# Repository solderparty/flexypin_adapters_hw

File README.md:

# FlexyPin Adapters

To learn more about FlexyPins, see the dedicated repo here: https://github.com/solderparty/flexypin

This repo contains a collection of open hardware designs for common modules that can be used with FlexyPins.

## ESP-12

## ESP32-C3-WROOM

## ESP32-S2-SOLO / ESP32-S3-WROOM

## ESP32-WROOM

## ESP32-WROVER

## M5Stamp-Pico

## RaspberryPi Pico

## RaspberryPi Pico to Uno

## RaspberryPi RM2

## RFM9x

## WIO RP2040

## Xiao / QTPy

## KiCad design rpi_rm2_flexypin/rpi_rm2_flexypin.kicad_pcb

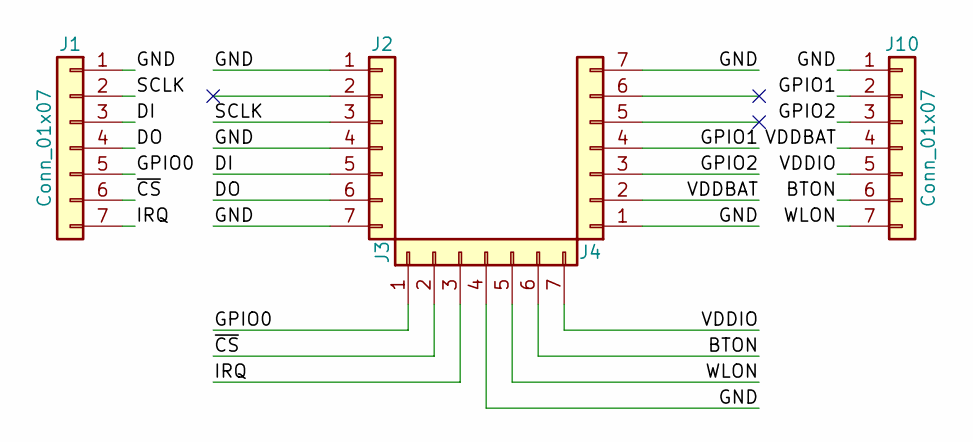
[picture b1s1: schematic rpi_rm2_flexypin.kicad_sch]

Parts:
J1, J10: Conn_01x07; PinHeader_1x07_P2.54mm_Vertical
J2, J3, J4: Conn_01x07; FlexyPin_1x07_P1.50mm

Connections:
/BTON: J3.6, J10.6
/DI: J1.3, J2.5
/DO: J1.4, J2.6
/GND: J1.1, J2.1, J2.4, J2.7, J3.4, J4.1, J4.7, J10.1
/GPIO0: J1.5, J3.1
/GPIO1: J4.4, J10.2
/GPIO2: J4.3, J10.3
/IRQ: J1.7, J3.3
/SCLK: J1.2, J2.3
/VDDBAT: J4.2, J10.4
/VDDIO: J3.7, J10.5
/WLON: J3.5, J10.7
/~CS: J1.6, J3.2

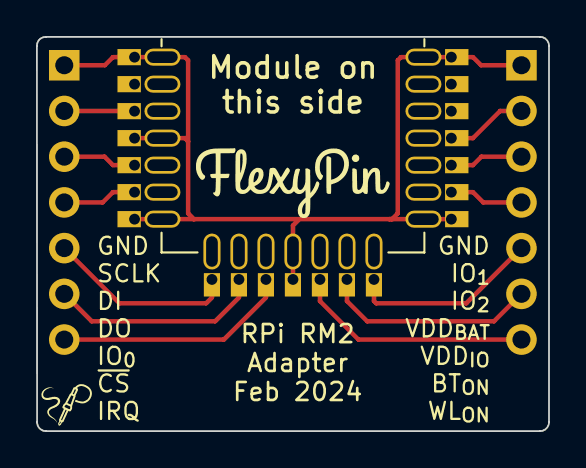
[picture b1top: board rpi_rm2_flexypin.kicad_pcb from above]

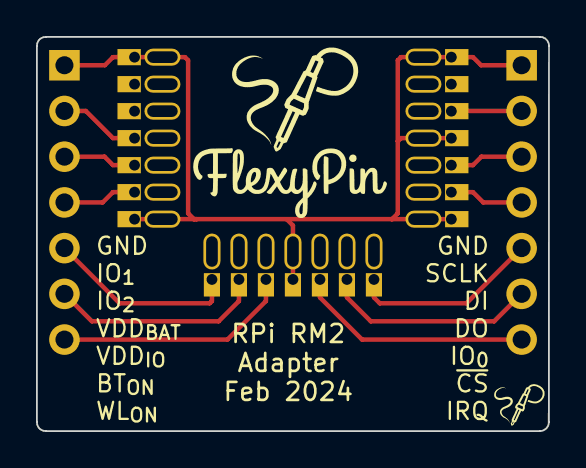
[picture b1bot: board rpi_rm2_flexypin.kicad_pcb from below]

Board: 2 copper layers, 28.5 x 21.9 mm, 5 parts (2 on the bottom side), 13 nets.

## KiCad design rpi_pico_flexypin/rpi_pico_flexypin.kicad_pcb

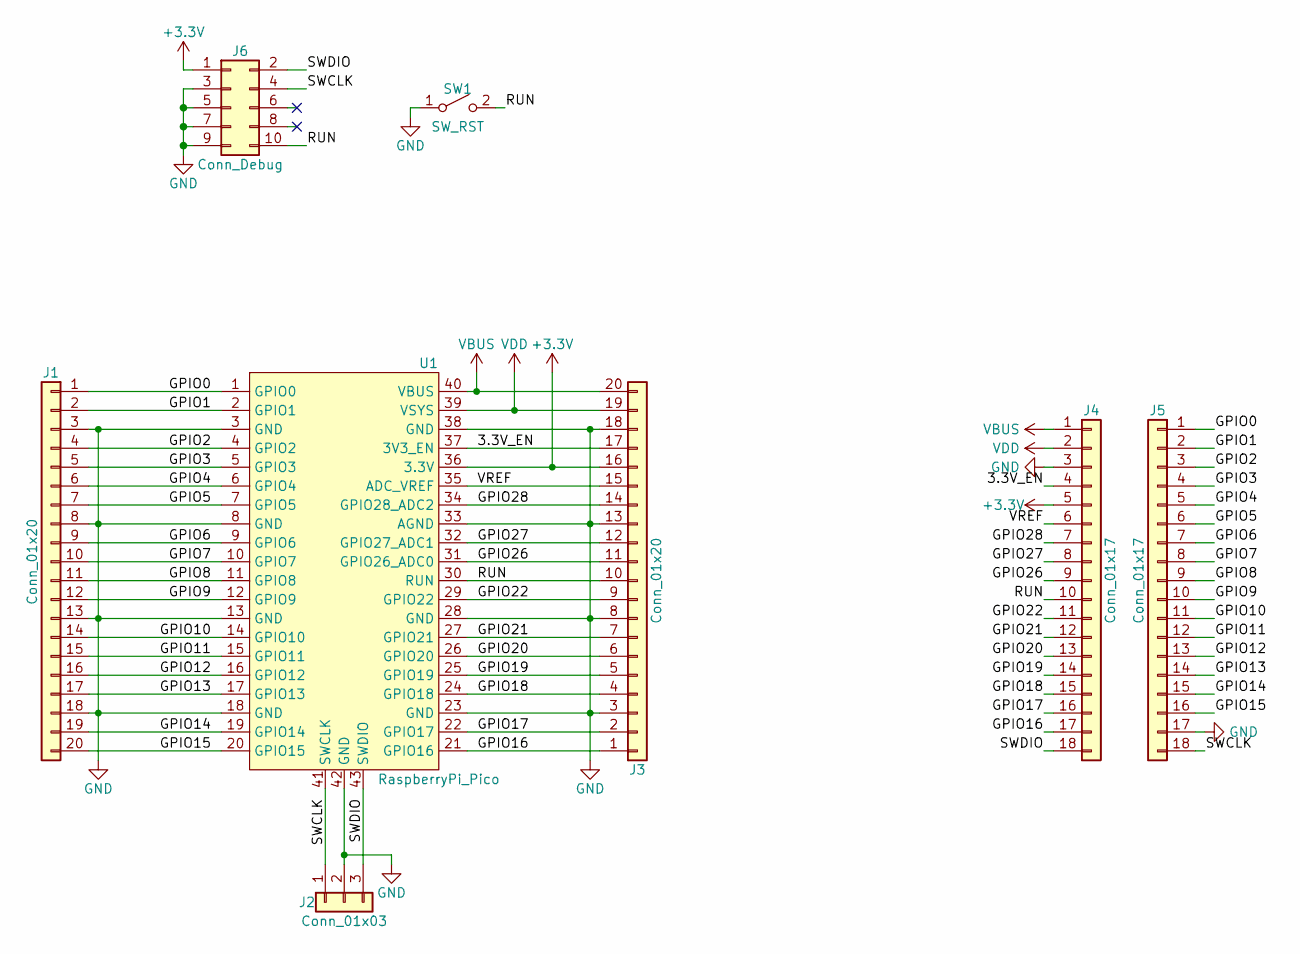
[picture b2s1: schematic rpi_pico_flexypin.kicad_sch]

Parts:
J1, J3: Conn_01x20; FlexyPin_1x20_P2.54mm
J2: Conn_01x03; FlexyPin_1x03_P2.54mm
J4, J5: Conn_01x17; PinHeader_1x18_P2.54mm_Vertical
J6: Conn_Debug; PinHeader_2x05_P1.27mm_Vertical_SMD_IDC
SW1: SW_RST; SW_Push_1P1T_NO_6x6mm_H9.5mm
U1: RaspberryPi_Pico

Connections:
+3V3: J3.16, J4.5, J6.1, U1.36 (3.3V)
/3.3V_EN: J3.17, J4.4, U1.37 (3V3_EN)
/GPIO0: J1.1, J5.1, U1.1 (GPIO0)
/GPIO1: J1.2, J5.2, U1.2 (GPIO1)
/GPIO2: J1.4, J5.3, U1.4 (GPIO2)
/GPIO3: J1.5, J5.4, U1.5 (GPIO3)
/GPIO4: J1.6, J5.5, U1.6 (GPIO4)
/GPIO5: J1.7, J5.6, U1.7 (GPIO5)
/GPIO6: J1.9, J5.7, U1.9 (GPIO6)
/GPIO7: J1.10, J5.8, U1.10 (GPIO7)
/GPIO8: J1.11, J5.9, U1.11 (GPIO8)
/GPIO9: J1.12, J5.10, U1.12 (GPIO9)
/GPIO10: J1.14, J5.11, U1.14 (GPIO10)
/GPIO11: J1.15, J5.12, U1.15 (GPIO11)
/GPIO12: J1.16, J5.13, U1.16 (GPIO12)
/GPIO13: J1.17, J5.14, U1.17 (GPIO13)
/GPIO14: J1.19, J5.15, U1.19 (GPIO14)
/GPIO15: J1.20, J5.16, U1.20 (GPIO15)
/GPIO16: J3.1, J4.17, U1.21 (GPIO16)
/GPIO17: J3.2, J4.16, U1.22 (GPIO17)
/GPIO18: J3.4, J4.15, U1.24 (GPIO18)
/GPIO19: J3.5, J4.14, U1.25 (GPIO19)
/GPIO20: J3.6, J4.13, U1.26 (GPIO20)
/GPIO21: J3.7, J4.12, U1.27 (GPIO21)
/GPIO22: J3.9, J4.11, U1.29 (GPIO22)
/GPIO26: J3.11, J4.9, U1.31 (GPIO26_ADC0)
/GPIO27: J3.12, J4.8, U1.32 (GPIO27_ADC1)
/GPIO28: J3.14, J4.7, U1.34 (GPIO28_ADC2)
/RUN: J3.10, J4.10, J6.10, SW1.2 (B), U1.30 (RUN)
/SWCLK: J2.1, J5.18, J6.4, U1.41 (SWCLK)
/SWDIO: J2.3, J4.18, J6.2, U1.43 (SWDIO)
/VREF: J3.15, J4.6, U1.35 (ADC_VREF)
GND: J1.3, J1.8, J1.13, J1.18, J2.2, J3.3, J3.8, J3.13, J3.18, J4.3, J5.17, J6.3, J6.5, J6.7, J6.9, SW1.1 (A), U1.3 (GND), U1.8 (GND), U1.13 (GND), U1.18 (GND), U1.23 (GND), U1.28 (GND), U1.33 (AGND), U1.38 (GND), U1.42 (GND)
VBUS: J3.20, J4.1, U1.40 (VBUS)
VDD: J3.19, J4.2, U1.39 (VSYS)

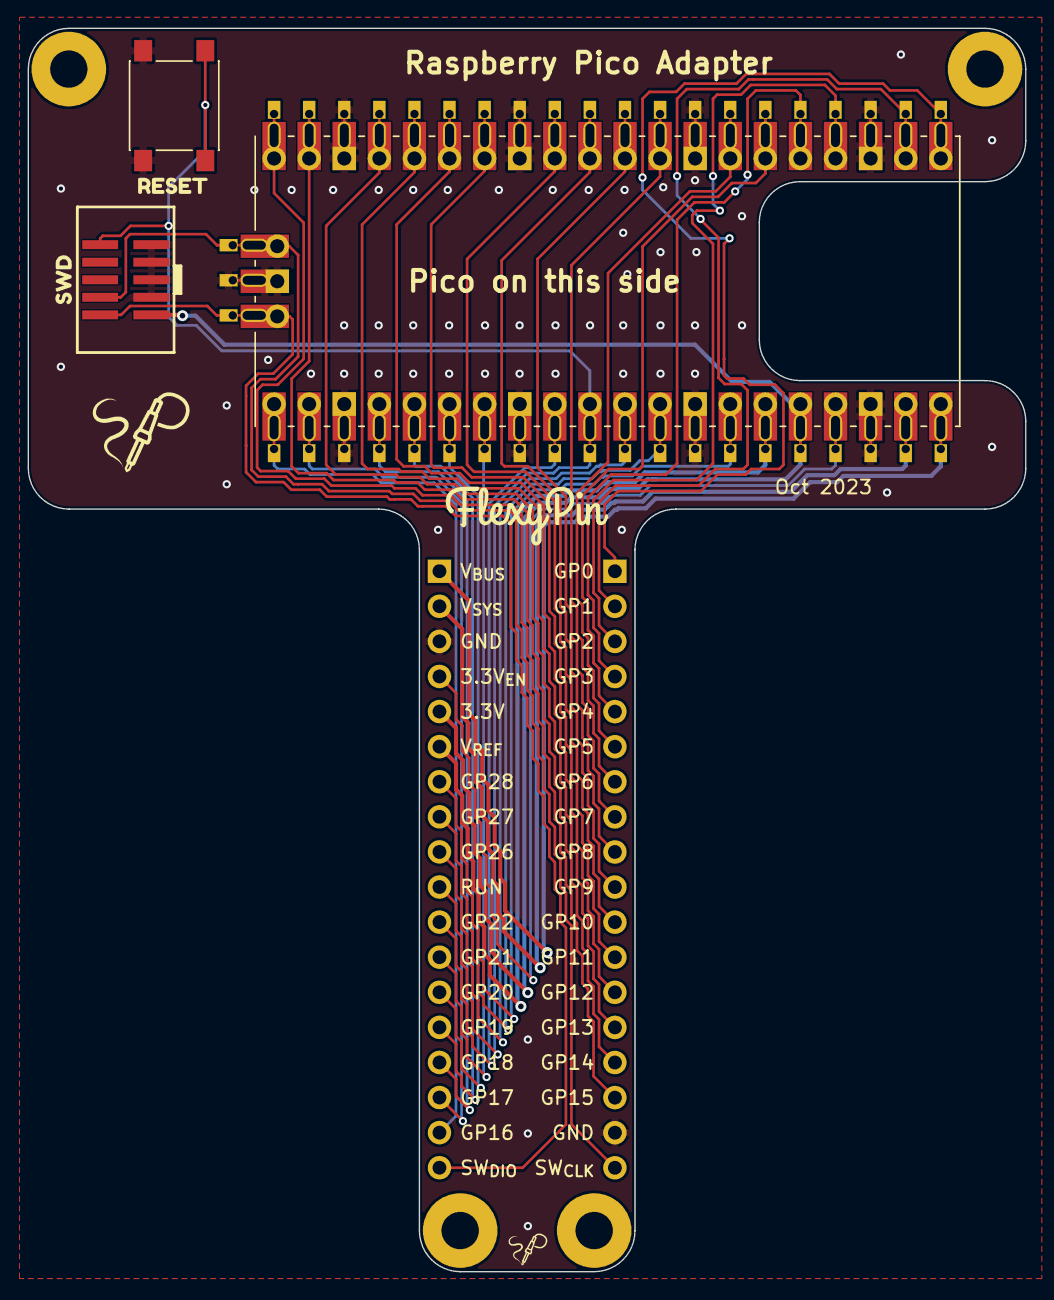
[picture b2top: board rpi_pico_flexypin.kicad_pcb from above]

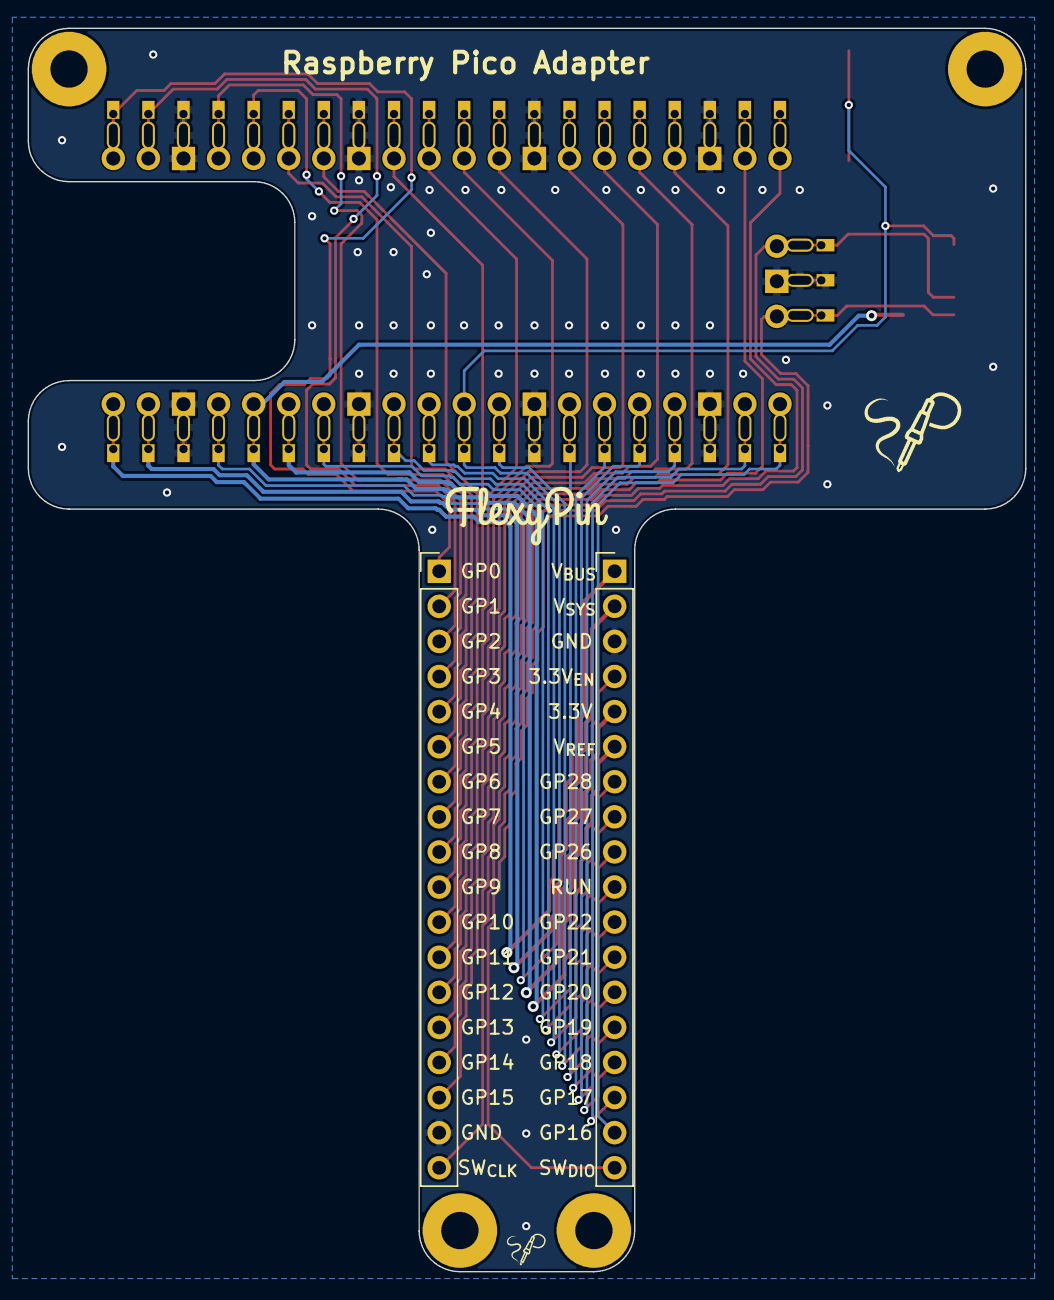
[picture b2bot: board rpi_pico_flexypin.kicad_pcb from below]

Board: 2 copper layers, 72.2 x 90.0 mm, 10 parts (2 on the bottom side), 35 nets.

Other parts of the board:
kibuzzard-6227DBEE: G***; kibuzzard-6227DBEE
kibuzzard-6227DBF8: G***; kibuzzard-6227DBF8

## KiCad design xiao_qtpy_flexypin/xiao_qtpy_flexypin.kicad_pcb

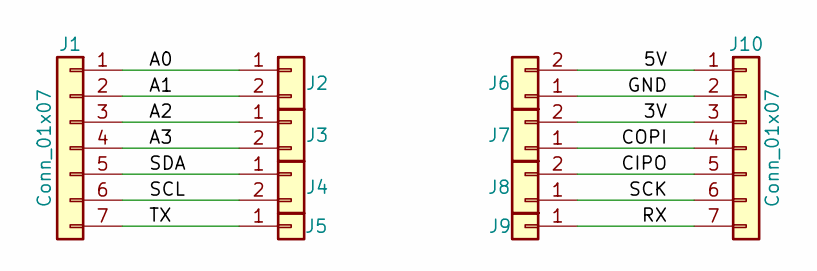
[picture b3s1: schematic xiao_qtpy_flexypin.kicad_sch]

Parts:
J1, J10: Conn_01x07; PinHeader_1x07_P2.54mm_Vertical
J2, J3, J4, J6, J7, J8: Conn_01x02; FlexyPin_1x02_P2.54mm
J5, J9: Conn_01x01; FlexyPin_1x01_P2.54mm

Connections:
/3V: J7.2, J10.3
/5V: J6.2, J10.1
/A0: J1.1, J2.1
/A1: J1.2, J2.2
/A2: J1.3, J3.1
/A3: J1.4, J3.2
/CIPO: J8.2, J10.5
/COPI: J7.1, J10.4
/GND: J6.1, J10.2
/RX: J9.1, J10.7
/SCK: J8.1, J10.6
/SCL: J1.6, J4.2
/SDA: J1.5, J4.1
/TX: J1.7, J5.1

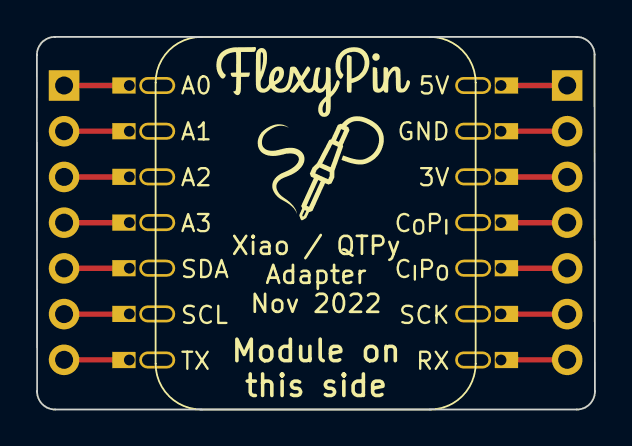
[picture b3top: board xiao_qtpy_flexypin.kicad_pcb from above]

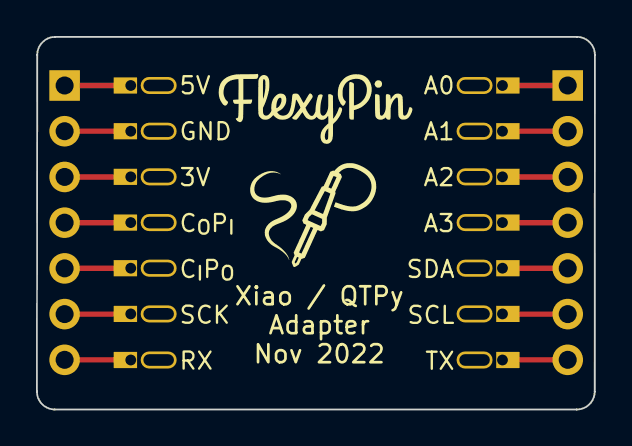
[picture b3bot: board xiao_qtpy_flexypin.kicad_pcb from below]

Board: 2 copper layers, 31.0 x 20.7 mm, 10 parts (2 on the bottom side), 14 nets.

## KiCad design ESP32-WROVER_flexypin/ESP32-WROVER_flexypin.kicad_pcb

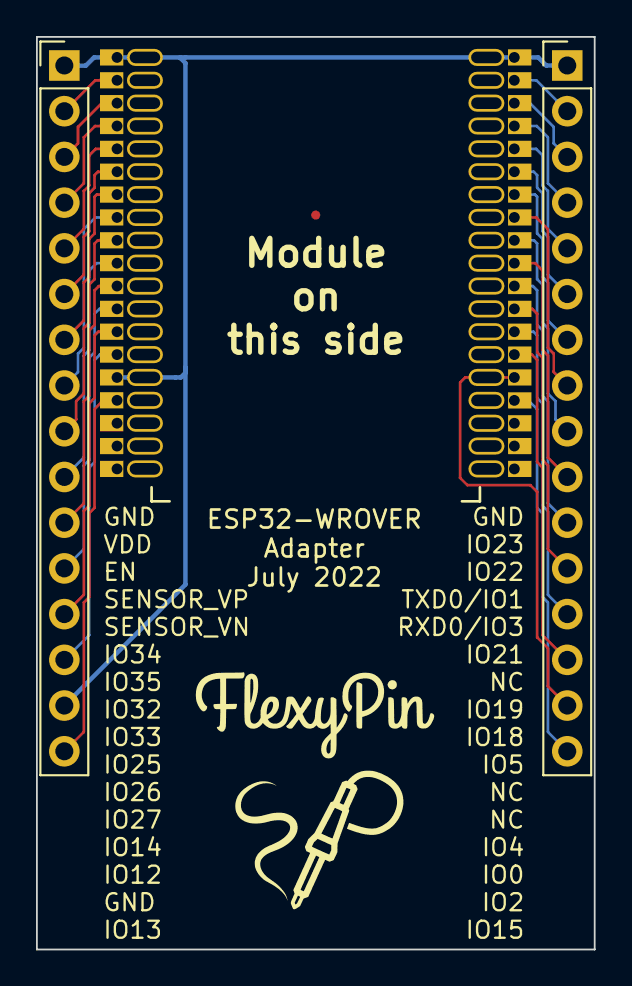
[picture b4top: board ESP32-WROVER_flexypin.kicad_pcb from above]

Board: 2 copper layers, 31.0 x 50.7 mm, 22 parts (0 on the bottom side), 30 nets.

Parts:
J1, J22: Conn_01x16; PinHeader_1x16_P2.54mm_Vertical
J2, J3, J4, J5, J6, J7, J8, J15, J16, J17, J18, J19, J20, J21, J24, J25, J26, J27: Conn_01x02; FlexyPin_1x02_P1.27mm
J12, J23: Conn_01x01; FlexyPin_1x01_P1.27mm

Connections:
/EN: J1.3, J24.2
/GND: J1.1, J1.15, J6.2, J12.1, J22.1, J23.1
/IO0: J19.2, J22.14
/IO2: J19.1, J22.15
/IO4: J18.1, J22.13
/IO5: J17.2, J22.10
/IO12: J1.14, J6.1
/IO13: J1.16, J7.1
/IO14: J1.13, J5.2
/IO15: J20.2, J22.16
/IO16: J18.2, J22.12
/IO17: J17.1, J22.11
/IO18: J16.1, J22.9
/IO19: J16.2, J22.8
/IO21: J15.2, J22.6
/IO22: J22.3, J25.1
/IO23: J22.2, J25.2
/IO25: J1.10, J4.1
/IO26: J1.11, J4.2
/IO27: J1.12, J5.1
/IO32: J1.8, J3.1
/IO33: J1.9, J3.2
/IO34: J1.6, J2.1
/IO35: J1.7, J2.2
/NC: J15.1, J22.7
/RXD0/IO3: J22.5, J27.1
/SENSOR_VN: J1.5, J26.2
/SENSOR_VP: J1.4, J26.1
/TXD0/IO1: J22.4, J27.2
/VDD: J1.2, J24.1

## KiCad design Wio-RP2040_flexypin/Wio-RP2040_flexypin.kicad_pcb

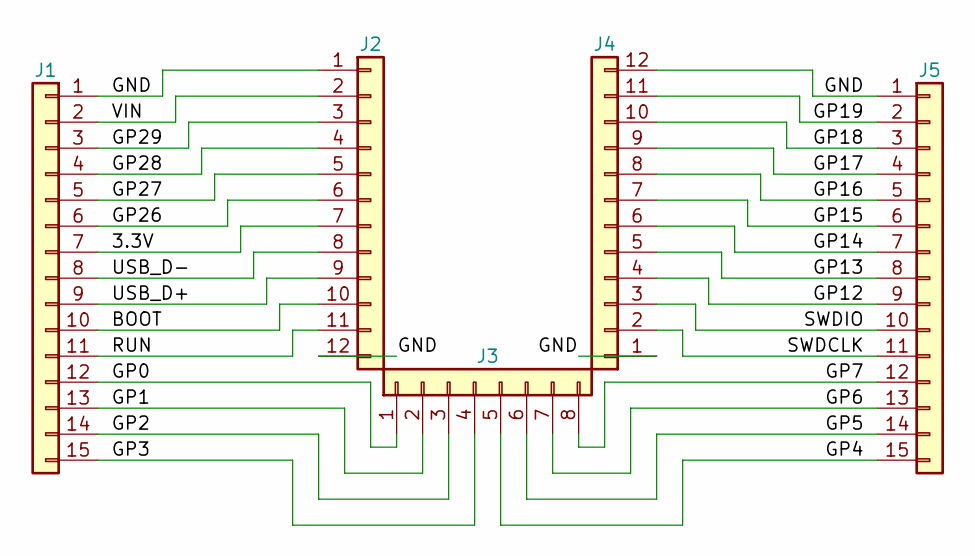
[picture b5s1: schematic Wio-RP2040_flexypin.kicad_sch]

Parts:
J1, J5: Conn_01x15; PinHeader_1x15_P2.54mm_Vertical
J2, J4: Conn_01x12; FlexyPin_1x12_P2.00mm
J3: Conn_01x08; FlexyPin_1x08_P2.00mm

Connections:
/3.3V: J1.7, J2.7
/BOOT: J1.10, J2.10
/GND: J1.1, J2.1, J2.12, J4.1, J4.12, J5.1
/GP0: J1.12, J3.1
/GP1: J1.13, J3.2
/GP2: J1.14, J3.3
/GP3: J1.15, J3.4
/GP4: J3.5, J5.15
/GP5: J3.6, J5.14
/GP6: J3.7, J5.13
/GP7: J3.8, J5.12
/GP12: J4.4, J5.9
/GP13: J4.5, J5.8
/GP14: J4.6, J5.7
/GP15: J4.7, J5.6
/GP16: J4.8, J5.5
/GP17: J4.9, J5.4
/GP18: J4.10, J5.3
/GP19: J4.11, J5.2
/GP26: J1.6, J2.6
/GP27: J1.5, J2.5
/GP28: J1.4, J2.4
/GP29: J1.3, J2.3
/RUN: J1.11, J2.11
/SWDCLK: J4.2, J5.11
/SWDIO: J4.3, J5.10
/USB_D+: J1.9, J2.9
/USB_D-: J1.8, J2.8
/VIN: J1.2, J2.2

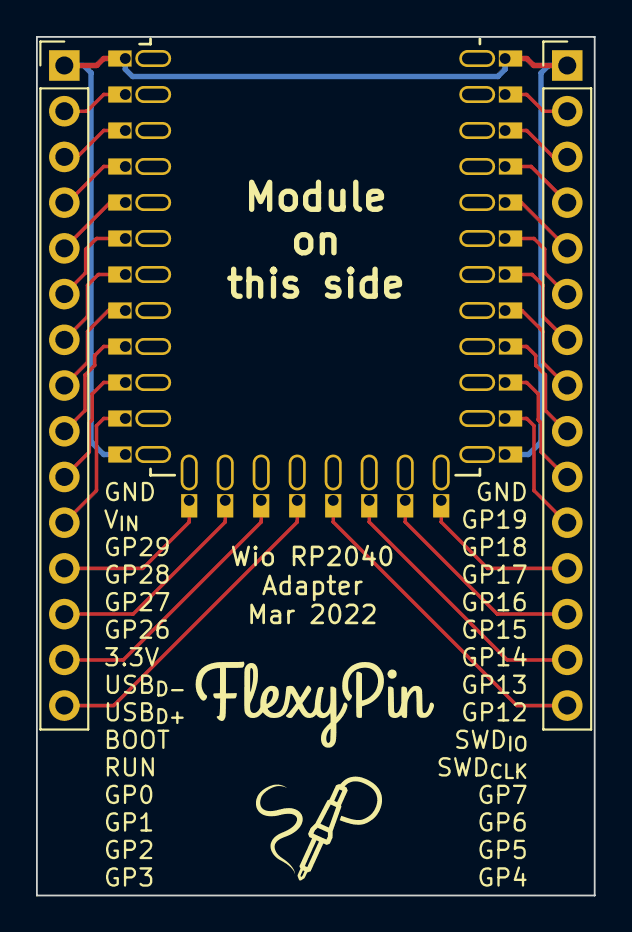
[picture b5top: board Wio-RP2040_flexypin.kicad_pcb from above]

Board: 2 copper layers, 31.0 x 47.7 mm, 5 parts (0 on the bottom side), 29 nets.

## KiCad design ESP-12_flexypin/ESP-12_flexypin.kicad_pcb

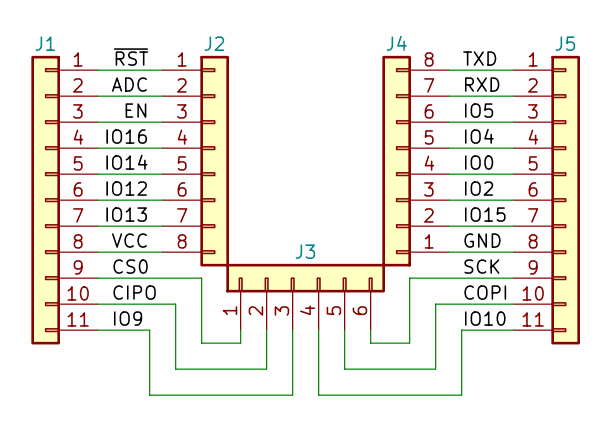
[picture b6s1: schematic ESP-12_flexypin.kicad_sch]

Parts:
J1, J5: Conn_01x11; PinHeader_1x11_P2.54mm_Vertical
J2, J4: Conn_01x08; FlexyPin_1x08_P2.00mm
J3: Conn_01x06; FlexyPin_1x06_P2.00mm

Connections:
/ADC: J1.2, J2.2
/CIPO: J1.10, J3.2
/COPI: J3.5, J5.10
/CS0: J1.9, J3.1
/EN: J1.3, J2.3
/GND: J4.1, J5.8
/IO0: J4.4, J5.5
/IO2: J4.3, J5.6
/IO4: J4.5, J5.4
/IO5: J4.6, J5.3
/IO9: J1.11, J3.3
/IO10: J3.4, J5.11
/IO12: J1.6, J2.6
/IO13: J1.7, J2.7
/IO14: J1.5, J2.5
/IO15: J4.2, J5.7
/IO16: J1.4, J2.4
/RXD: J4.7, J5.2
/SCK: J3.6, J5.9
/TXD: J4.8, J5.1
/VCC: J1.8, J2.8
/~RST: J1.1, J2.1

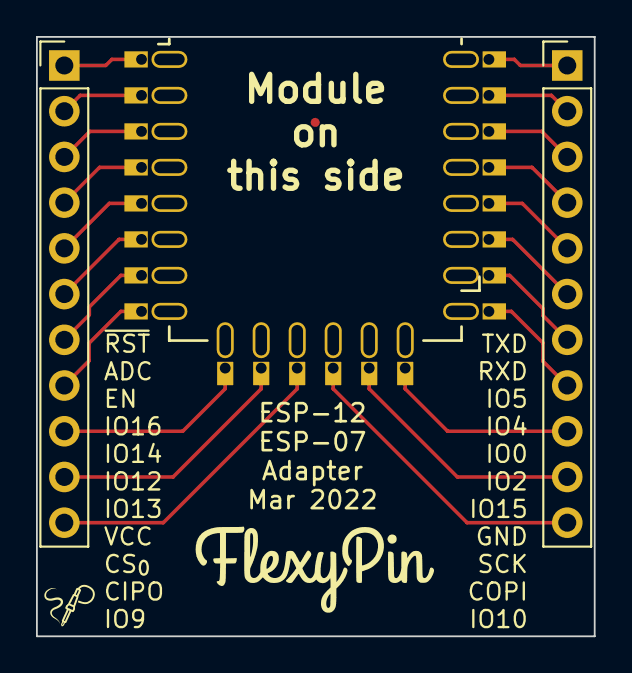
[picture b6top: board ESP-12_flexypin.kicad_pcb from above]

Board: 2 copper layers, 31.0 x 33.3 mm, 5 parts (0 on the bottom side), 22 nets.

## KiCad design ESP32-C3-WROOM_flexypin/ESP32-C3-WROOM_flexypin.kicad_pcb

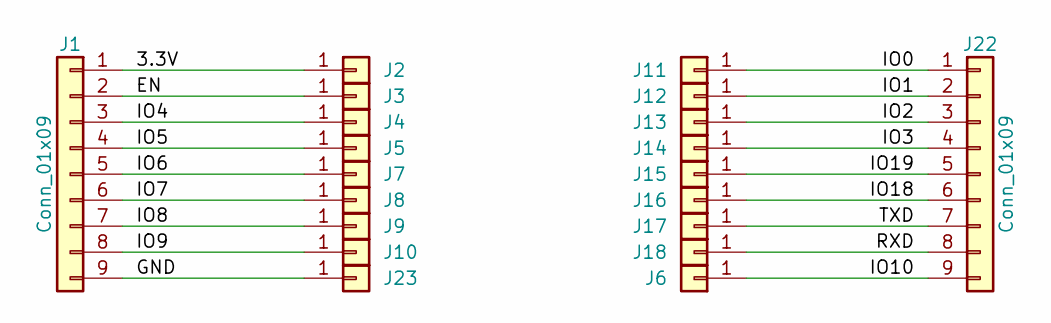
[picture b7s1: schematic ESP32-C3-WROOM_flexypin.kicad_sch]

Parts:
J1, J22: Conn_01x09; PinHeader_1x09_P2.54mm_Vertical
J2, J3, J4, J5, J6, J7, J8, J9, J10, J11, J12, J13, J14, J15, J16, J17, J18, J23: Conn_01x01; FlexyPin_1x01

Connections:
/3.3V: J1.1, J2.1
/EN: J1.2, J3.1
/GND: J1.9, J23.1
/IO0: J11.1, J22.1
/IO1: J12.1, J22.2
/IO2: J13.1, J22.3
/IO3: J14.1, J22.4
/IO4: J1.3, J4.1
/IO5: J1.4, J5.1
/IO6: J1.5, J7.1
/IO7: J1.6, J8.1
/IO8: J1.7, J9.1
/IO9: J1.8, J10.1
/IO10: J6.1, J22.9
/IO18: J16.1, J22.6
/IO19: J15.1, J22.5
/RXD: J18.1, J22.8
/TXD: J17.1, J22.7

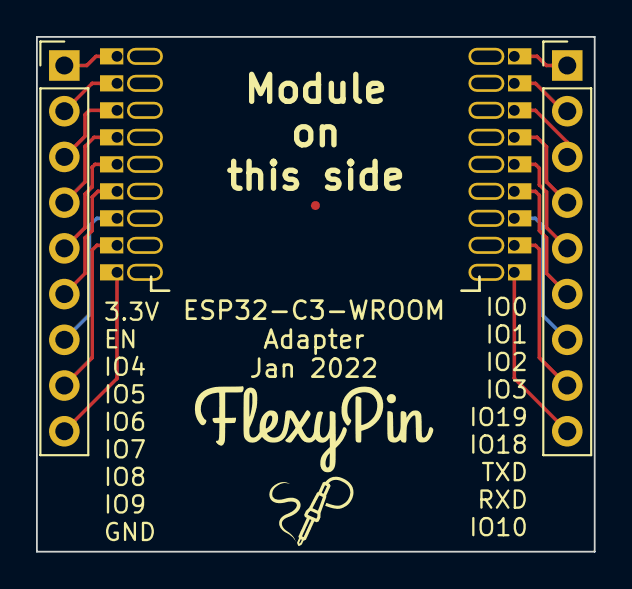
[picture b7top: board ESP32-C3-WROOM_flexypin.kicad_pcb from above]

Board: 2 copper layers, 31.0 x 28.6 mm, 20 parts (0 on the bottom side), 18 nets.

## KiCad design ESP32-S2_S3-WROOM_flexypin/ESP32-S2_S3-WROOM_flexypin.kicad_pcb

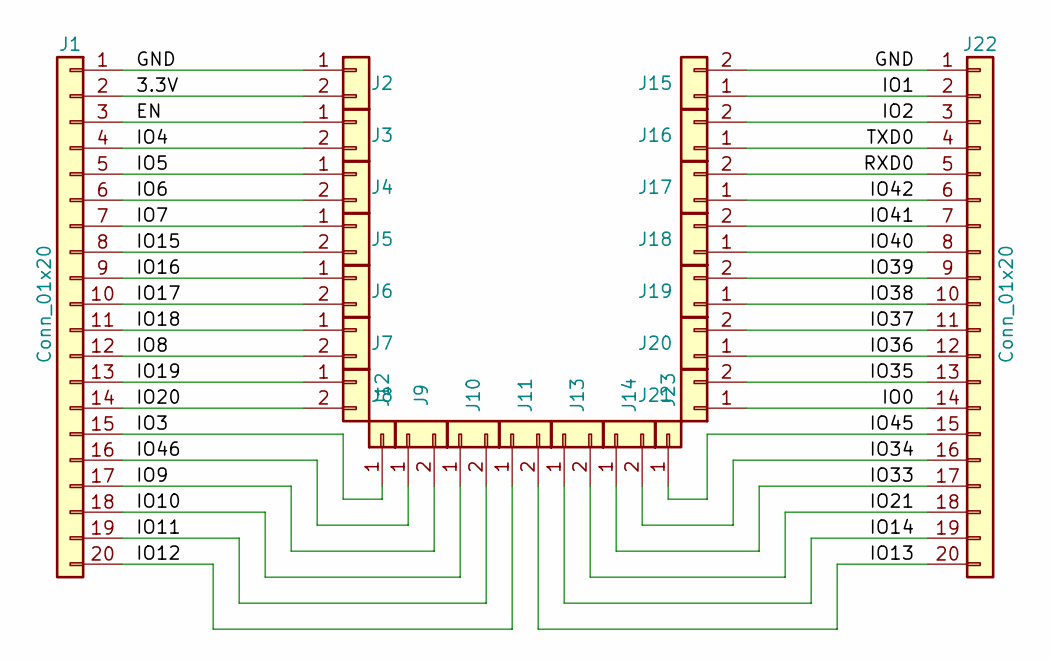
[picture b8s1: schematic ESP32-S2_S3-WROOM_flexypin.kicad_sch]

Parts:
J1, J22: Conn_01x20; PinHeader_1x20_P2.54mm_Vertical
J2, J3, J4, J5, J6, J7, J8, J9, J10, J11, J13, J14, J15, J16, J17, J18, J19, J20, J21: Conn_01x02; FlexyPin_1x02_P1.27mm
J12, J23: Conn_01x01; FlexyPin_1x01

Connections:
/3.3V: J1.2, J2.2
/EN: J1.3, J3.1
/GND: J1.1, J2.1, J15.2, J22.1
/IO0: J21.1, J22.14
/IO1: J15.1, J22.2
/IO2: J16.2, J22.3
/IO3: J1.15, J12.1
/IO4: J1.4, J3.2
/IO5: J1.5, J4.1
/IO6: J1.6, J4.2
/IO7: J1.7, J5.1
/IO8: J1.12, J7.2
/IO9: J1.17, J9.2
/IO10: J1.18, J10.1
/IO11: J1.19, J10.2
/IO12: J1.20, J11.1
/IO13: J11.2, J22.20
/IO14: J13.1, J22.19
/IO15: J1.8, J5.2
/IO16: J1.9, J6.1
/IO17: J1.10, J6.2
/IO18: J1.11, J7.1
/IO19: J1.13, J8.1
/IO20: J1.14, J8.2
/IO21: J13.2, J22.18
/IO33: J14.1, J22.17
/IO34: J14.2, J22.16
/IO35: J21.2, J22.13
/IO36: J20.1, J22.12
/IO37: J20.2, J22.11
/IO38: J19.1, J22.10
/IO39: J19.2, J22.9
/IO40: J18.1, J22.8
/IO41: J18.2, J22.7
/IO42: J17.1, J22.6
/IO45: J22.15, J23.1
/IO46: J1.16, J9.1
/RXD0: J17.2, J22.5
/TXD0: J16.1, J22.4

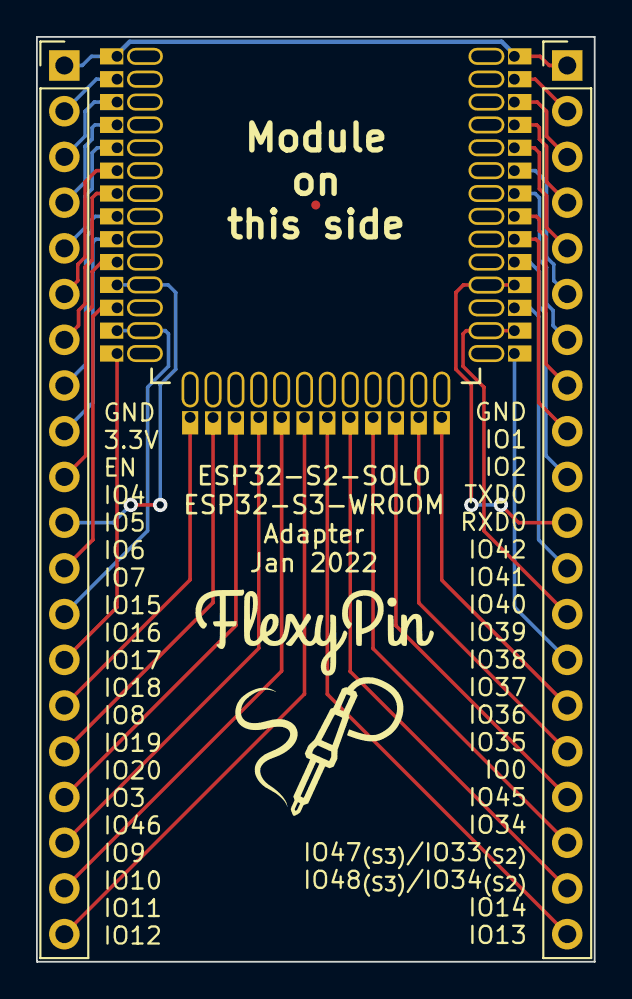
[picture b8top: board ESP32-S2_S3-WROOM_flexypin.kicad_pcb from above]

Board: 2 copper layers, 31.0 x 51.4 mm, 23 parts (0 on the bottom side), 39 nets.

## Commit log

2022-03-03 Initial import
2022-03-24 Ignore & remove cache files
2022-03-25 Backport to KiCad v6 (stable)
2022-04-05 Add RPi Pico Adapter
2022-04-05 Fix up 3D models
2022-04-05 Add ESP-12/ESP-07/ESP8266MOD Adapter
2022-04-05 Add images for the new adapters
2022-05-09 Add Wio RP2040
2022-09-11 Add ESP32 WROVER
2022-09-11 Add RPi Pico to Uno
2022-12-19 Add Xiao/QTPy
2023-10-30 Change Pico Adapters' Reset Button to SMD
2025-03-22 Add RPi RM2
